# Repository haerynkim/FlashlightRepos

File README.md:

# FlashlightRepos
Final video submission URL: https://youtu.be/8UVXDF8A7WE<br/>
*note: I did not indicate on Sakai but I submitted course evaluations in class.

## How To
This design is protable lightbox and pulse sensor. To turn the device on, toggle the switch ON. An initiation screen will appear and in a few seconds, the red LED will turn on. To cycle through various modes, simply push down on the pushbutton. On every fourth push of the cycle, the LCD will display the pulse readings. You can attach or detach the pulse sensor at any moment by attaching or removing the earclip to your earlobes.<br/>
To replace the battery, simply open the box and unscrew the 1/8" bolts and expose the battery underneath. The battery cap is easily removable, and the battery replaceable.

## Features of the Device

### Software
* Debounce, interrupt on pushbutton
* Max BPM resets if max BPM remains over 215 bpm for greater than 20 seconds

### Hardware
* Green 3mm LED on PCB to indicate connection to power source and battery life (with diminishing brightness)
* 5.5 x 4.0 (cm) double-sided PCB with ground plane

### Mechanical
* Easy mount, easy install
* Tight latch and hinge design
* (-) LED without lightpipe

### Extra
* Pulse sensor: measures pulse at 9600 bauds rate. Can be attached to earlobe or finger.
* LED display: "Haeryn's Light Box: Thank You Matt Brown!" logo and continous display of current BPM and max BPM
* Indicates maximum BPM measured since device turned ON.

### Extra specifications

| Spec | Measured |
|-----------------|--------|
| Size(cm)        | 6x7x5  |
| Weight(g)       | 127.6g |
| Power draw(mA)  | 65-70  |
| Runtime ON(hr)  | 8.90   |
| Runtime OFF(hr) | inf    |
| Cost($)         | 35.15  |

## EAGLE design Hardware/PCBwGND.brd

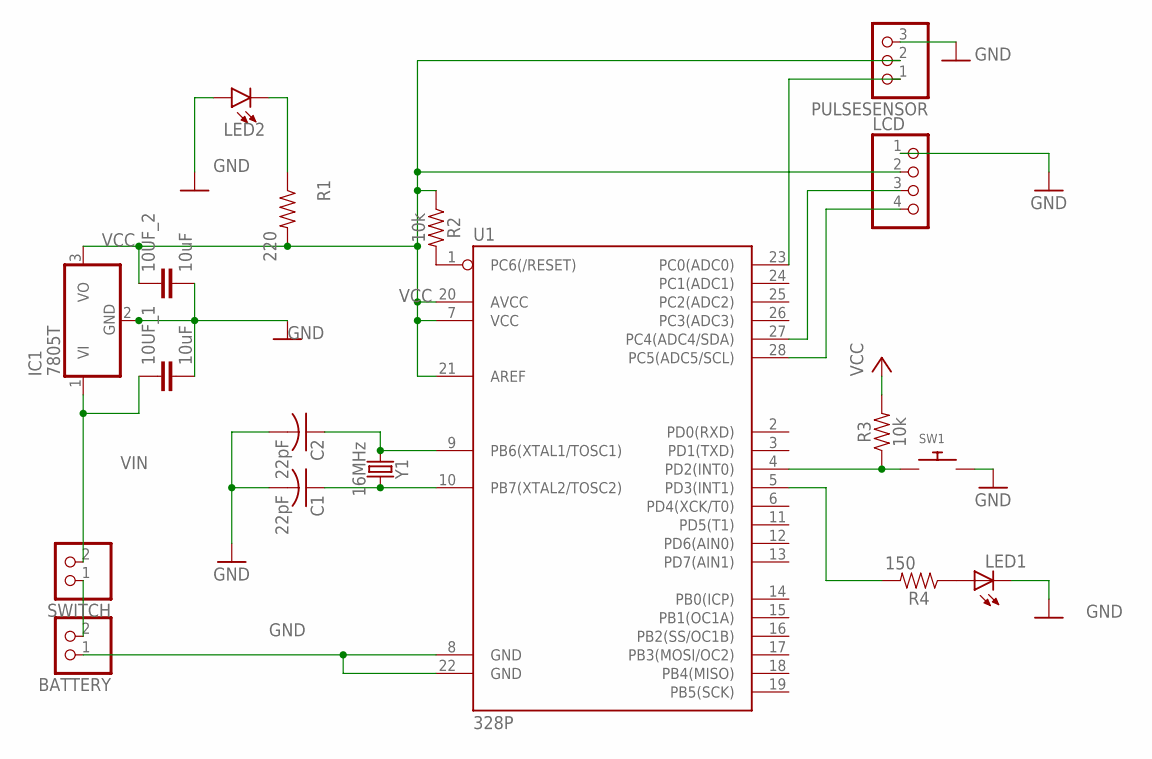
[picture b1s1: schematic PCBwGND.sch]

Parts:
10UF_1, 10UF_2: 10uF; CAP-PTH-2.54
BATTERY: PINHD-1X2; 1X02
C1, C2: 22pF; C025-024X044
IC1: 7805T; TO220H
LCD: PINHD-1X4; 1X04
LED1: LED5MM
LED2: LED3MM; LED_3MM
PULSESENSOR: PINHD-1X3; 1X03
R1: 220; AXIAL-0.3
R2, R3: 10k; AXIAL-0.3
R4: 150; AXIAL-0.3
SW1: SWITCH_PUSHBUTTONEVQ-PE; TACT_PANA-EVQ
SWITCH: PINHD-1X2; 1X02
U1: 328P; DIP28
Y1: 16MHz; HC49US

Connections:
GND: 10UF_1.2, 10UF_2.2, BATTERY.1, C1.2, C2.2, IC1.2 (GND), LCD.1, LED1.K (C), LED2.A, PULSESENSOR.3, SW1.P$2, U1.8 (GND), U1.22 (GND)
unnamed: BATTERY.2, SWITCH.1
unnamed: LED1.A, R4.P$1 (1)
unnamed: LED2.K (C), R1.P$1 (1)
PC0/ADC0: PULSESENSOR.1, U1.23 (PC0(ADC0))
PD2: R4.P$2 (2), U1.5 (PD3(INT1))
PD3: R3.P$1 (1), SW1.P$1, U1.4 (PD2(INT0))
RESET: R2.P$2 (2), U1.1 (PC6(/RESET))
SCL: LCD.4, U1.28 (PC5(ADC5/SCL))
SDA: LCD.3, U1.27 (PC4(ADC4/SDA))
VCC: 10UF_2.1, IC1.3 (VO), LCD.2, PULSESENSOR.2, R1.P$2 (2), R2.P$1 (1), R3.P$2 (2), U1.7 (VCC), U1.20 (AVCC), U1.21 (AREF)
VIN: 10UF_1.1, IC1.1 (VI), SWITCH.2
XTAL1: C2.1, U1.9 (PB6(XTAL1/TOSC1)), Y1.1
XTAL2: C1.1, U1.10 (PB7(XTAL2/TOSC2)), Y1.2

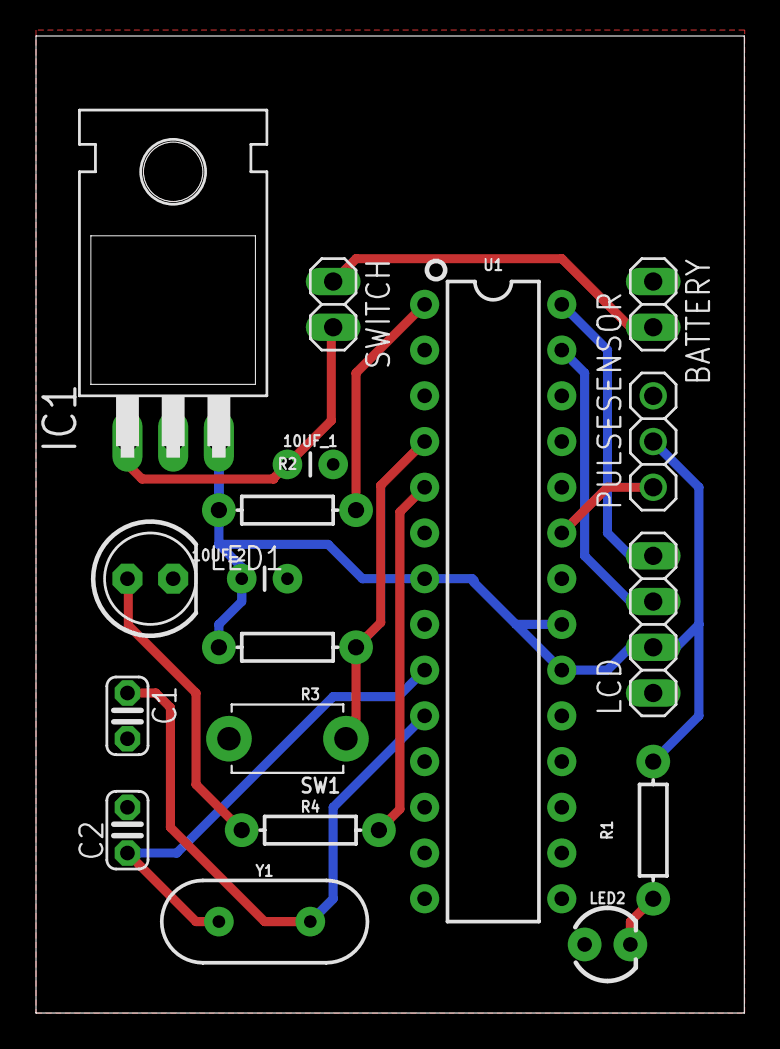
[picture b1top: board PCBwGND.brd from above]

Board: 2 copper layers, 39.4 x 54.3 mm, 18 parts (0 on the bottom side), 14 nets.

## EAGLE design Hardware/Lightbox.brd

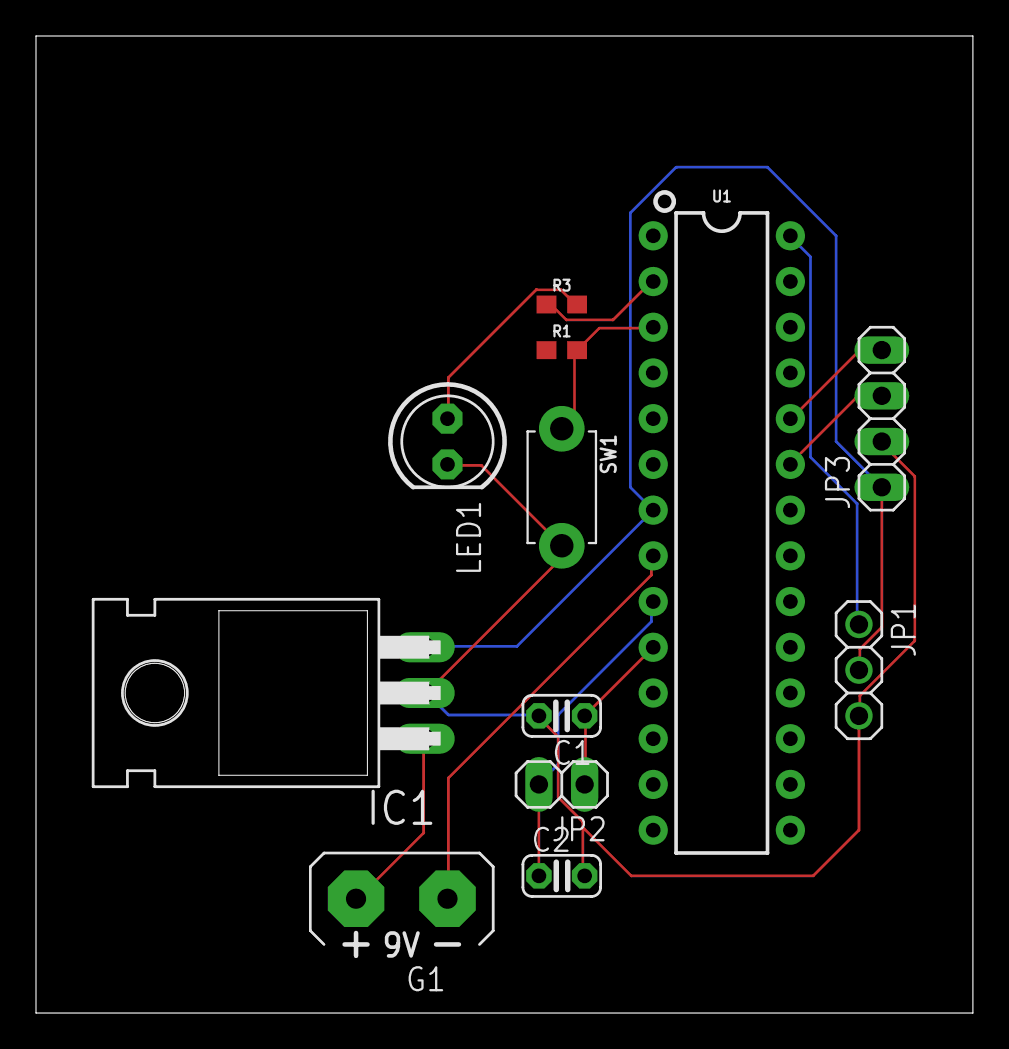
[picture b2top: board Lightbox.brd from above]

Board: 2 copper layers, 52.0 x 54.3 mm, 12 parts (0 on the bottom side), 12 nets.

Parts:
C1, C2: 22pF; C025-024X044
G1: AB9V
IC1: 7805T; TO220H
JP1: 1X03
JP2: 1X02
JP3: 1X04
LED1: LED5MM
R1, R3: 150; 0603
SW1: TACT_PANA-EVQ
U1: 328P; DIP28

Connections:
GND: C1.2, C2.2, IC1.2, JP1.3, JP3.2, LED1.K, SW1.P$2
unnamed: JP3.3, U1.23
unnamed: JP3.4, U1.24
unnamed: G1.+, IC1.1
unnamed: G1.-, U1.8
unnamed: IC1.3, JP1.2, JP3.1, U1.7
unnamed: LED1.A, R3.2
unnamed: R3.1, U1.2
unnamed: C2.1, JP2.2, U1.9
unnamed: C1.1, JP2.1, U1.10
unnamed: R1.2, SW1.P$1, U1.3
unnamed: JP1.1, U1.28

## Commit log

2018-09-20 Edit README.md
2018-09-20 add initial file in Mechanical
2018-09-20 more initial files in this repository
2018-10-01 Update README.md for Milestone 01
2018-10-01 Add block diagram and design sketch
2018-10-19 Add Arduino code ButtonBlink.ino
    Makes the switch button work with one LED function.
2018-10-31 Milestone 02 Assignments
2018-10-31 Add Milestone03 assignments for review
2018-11-05 Adding backup iterations of working Arduino code
2018-11-06 Add file of working heart rate monitor version with fixed threshold
2018-11-06 Add code to initialize Seeed OLED Display
2018-11-08 add file that reads analog signal and calculates hr
2018-11-12 Add working version Eagle schematic and PCB for initial review
2018-11-12 Moved directories of software_code.md
2018-11-12 Rename Electronics folder as Hardware for milestone04
2018-11-12 Added missing values and correct connections to Atmega328p
2018-11-12 Move into respective folders
2018-11-12 Working code that reads BPM from pulse sensor without hard-coded threshold
2018-11-12 Arduino libraries for SeeedOLED display and PulseSensor
2018-11-12 Add code to activate and output values onto LCD
2018-11-12 Solve issue with overwriting digits on LCD display and add logo for initial setup display
2018-11-15 Increase trace thickness and replace wrong components
2018-11-19 Add dimensions and replace battery with 2pin header
2018-11-19 milestone 05 2d drawing and 3d fusion360 model
2018-11-19 Update WorkingBPM.ino
    Add constraint for max BPM reading. Code recorded in demo #2.
2018-11-19 Add first test demo videdeo with WorkingBPM code
2018-11-20 Schematic and PCB design for final review
2018-11-28 Arduino to Breadboard working video
2018-11-29 Add Final PCB design and remove first PCB iteration
2018-11-29 Add ground plane to reduce photoetching area
2018-12-03 Add new hinged box design for modified PCB. Added parametric design.
2018-12-04 Update CAD design with latch
2018-12-04 Add video of PCB and all components working
2018-12-14 Push all necessary files, clean directories
2018-12-14 Re-do previous commit before too-large sized file

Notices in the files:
parts and their libraries:
SparkFun-Resistors: Licensing: Creative Commons ShareAlike 4.0 International - https://creativecommons.org/licenses/by-sa/4.0
